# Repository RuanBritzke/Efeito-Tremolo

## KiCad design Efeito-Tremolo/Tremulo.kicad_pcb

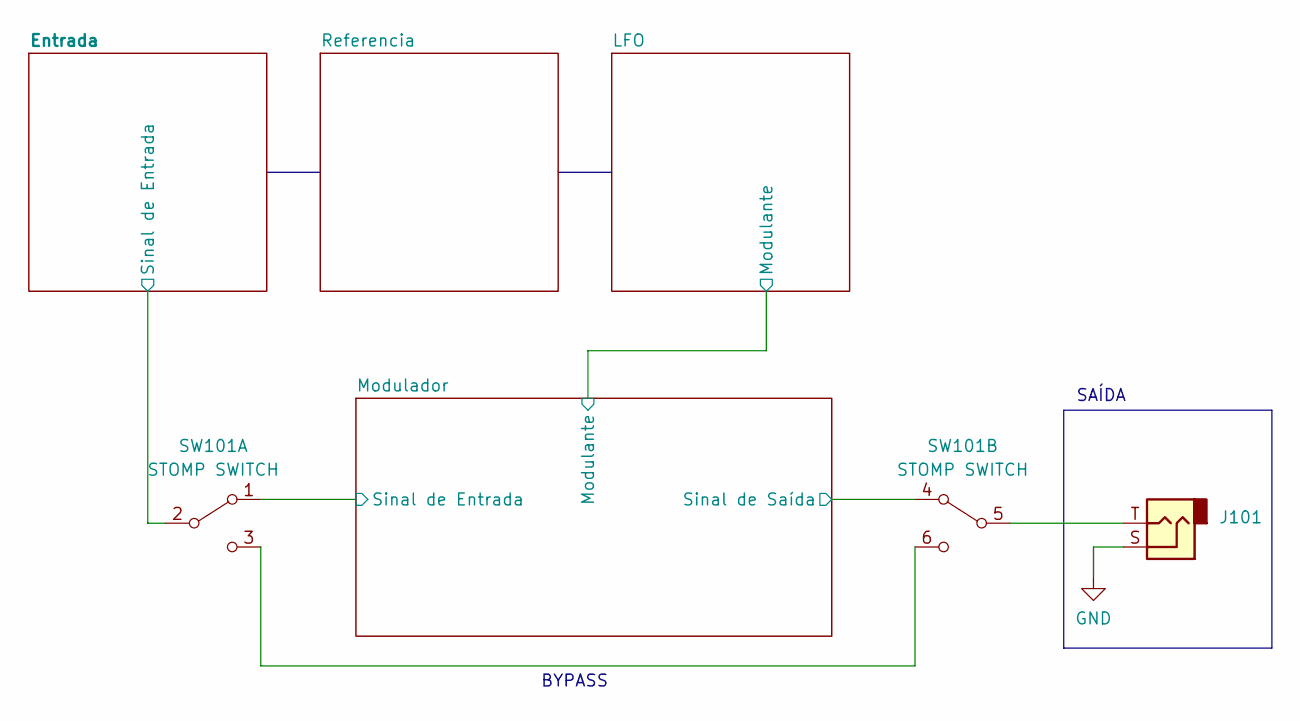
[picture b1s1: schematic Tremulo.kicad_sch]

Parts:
J101: AudioJack2; PinHeader_1x02_P2.54mm_Vertical
SW101: STOMP SWITCH; PinHeader_2x03_P2.54mm_Vertical

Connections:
/Entrada/Sinal de Entrada: SW101.2 (B); also elsewhere on the board
/Modulador/Sinal de Entrada: SW101.1 (A); also elsewhere on the board
/Modulador/Sinal de Saída: SW101.4 (A); also elsewhere on the board
GND: J101.S; also elsewhere on the board
unnamed: J101.T, SW101.5 (B)
unnamed: SW101.3 (C), SW101.6 (C)

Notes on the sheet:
BYPASS
SAÍDA

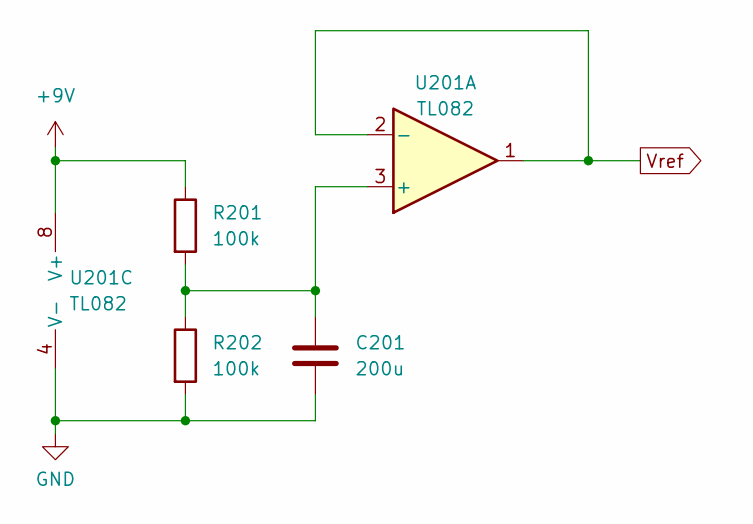
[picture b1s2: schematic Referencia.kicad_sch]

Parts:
C201: 200u; CP_Radial_D8.0mm_P5.00mm
R201, R202: 100k; R_Box_L8.4mm_W2.5mm_P5.08mm
U201: TL082; DIP-8_W7.62mm

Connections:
GND: C201.2, R202.2, U201.4 (V-); also elsewhere on the board
unnamed: C201.1, R201.2, R202.1, U201.3 (+)
Vref: U201.1, U201.2 (-); also elsewhere on the board

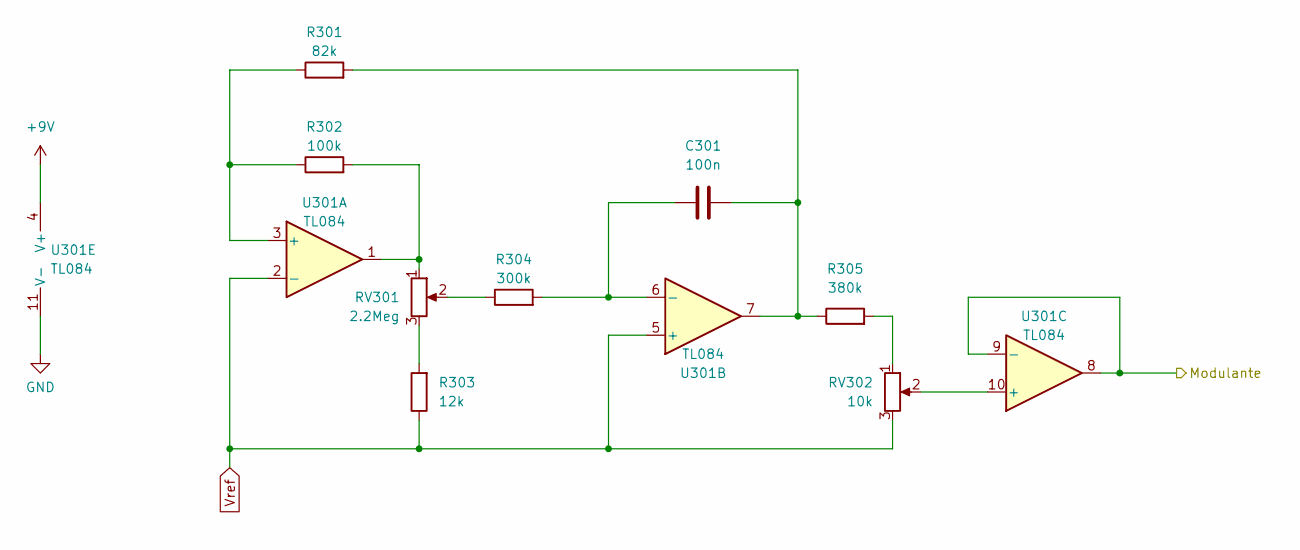
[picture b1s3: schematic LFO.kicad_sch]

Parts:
C301: 100n; CP_Radial_D8.0mm_P5.00mm
R301: 82k; R_Box_L8.4mm_W2.5mm_P5.08mm
R302: 100k; R_Box_L8.4mm_W2.5mm_P5.08mm
R303: 12k; R_Box_L8.4mm_W2.5mm_P5.08mm
R304: 300k; R_Box_L8.4mm_W2.5mm_P5.08mm
R305: 380k; R_Box_L8.4mm_W2.5mm_P5.08mm
RV301: 2.2Meg; PinHeader_1x03_P2.54mm_Vertical
RV302: 10k; PinHeader_1x03_P2.54mm_Vertical
U301: TL084; DIP-14_W7.62mm

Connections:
/LFO/Modulante: U301.8, U301.9 (-); also elsewhere on the board
GND: U301.11 (V-); also elsewhere on the board
unnamed: C301.1, R301.2, R305.1, U301.7
unnamed: C301.2, R304.2, U301.6 (-)
unnamed: R301.1, R302.1, U301.3 (+)
unnamed: R302.2, RV301.1, U301.1
unnamed: R303.2, RV301.3
unnamed: R304.1, RV301.2
unnamed: R305.2, RV302.1
unnamed: RV302.2, U301.10 (+)
Vref: R303.1, RV302.3, U301.2 (-), U301.5 (+); also elsewhere on the board

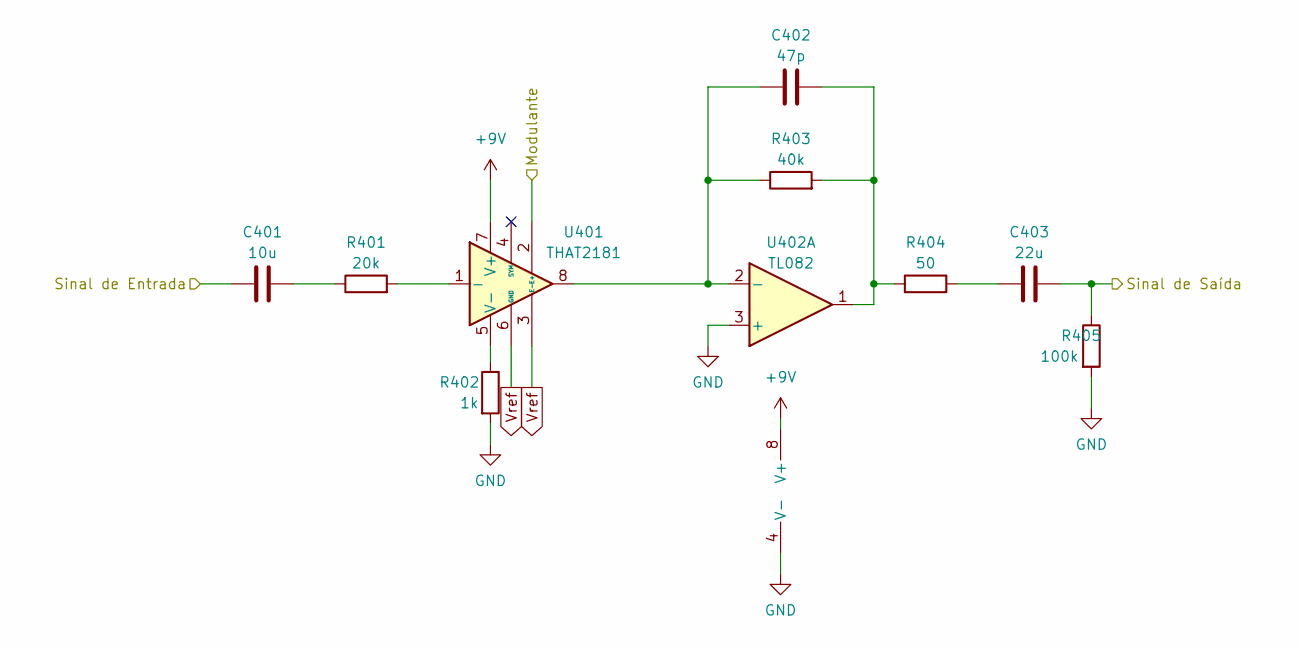
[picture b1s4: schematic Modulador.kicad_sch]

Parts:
C401: 10u; CP_Radial_D8.0mm_P5.00mm
C402: 47p; CP_Radial_D8.0mm_P5.00mm
C403: 22u; CP_Radial_D8.0mm_P5.00mm
R401: 20k; R_Box_L8.4mm_W2.5mm_P5.08mm
R402: 1k; R_Box_L8.4mm_W2.5mm_P5.08mm
R403: 40k; R_Box_L8.4mm_W2.5mm_P5.08mm
R404: 50; R_Box_L8.4mm_W2.5mm_P5.08mm
R405: 100k; R_Box_L8.4mm_W2.5mm_P5.08mm
U401: THAT2181; SIP-8_19x3mm_P2.54mm
U402: TL082; DIP-8_W7.62mm

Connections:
/LFO/Modulante: U401.2 (E+); also elsewhere on the board
/Modulador/Sinal de Entrada: C401.1; also elsewhere on the board
/Modulador/Sinal de Saída: C403.1, R405.1; also elsewhere on the board
GND: R402.2, R405.2, U402.3 (+), U402.4 (V-); also elsewhere on the board
unnamed: C401.2, R401.1
unnamed: C402.1, R403.1, U401.8, U402.2 (-)
unnamed: C402.2, R403.2, R404.2, U402.1
unnamed: C403.2, R404.1
unnamed: R401.2, U401.1 (-)
unnamed: R402.1, U401.5 (V-)
Vref: U401.3 (E-), U401.6 (GND); also elsewhere on the board

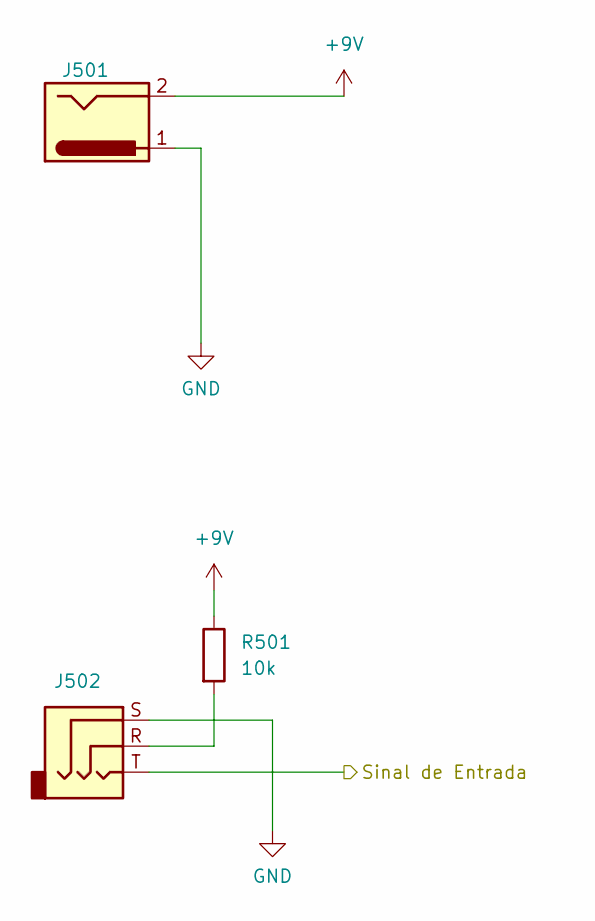
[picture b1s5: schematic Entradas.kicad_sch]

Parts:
J501: Barrel_Jack; PinHeader_1x02_P2.54mm_Vertical
J502: AudioJack3; PinHeader_1x03_P2.54mm_Vertical
R501: 10k; R_Box_L8.4mm_W2.5mm_P5.08mm

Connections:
/Entrada/Sinal de Entrada: J502.T; also elsewhere on the board
GND: J501.1, J502.S; also elsewhere on the board
unnamed: J502.R, R501.2

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
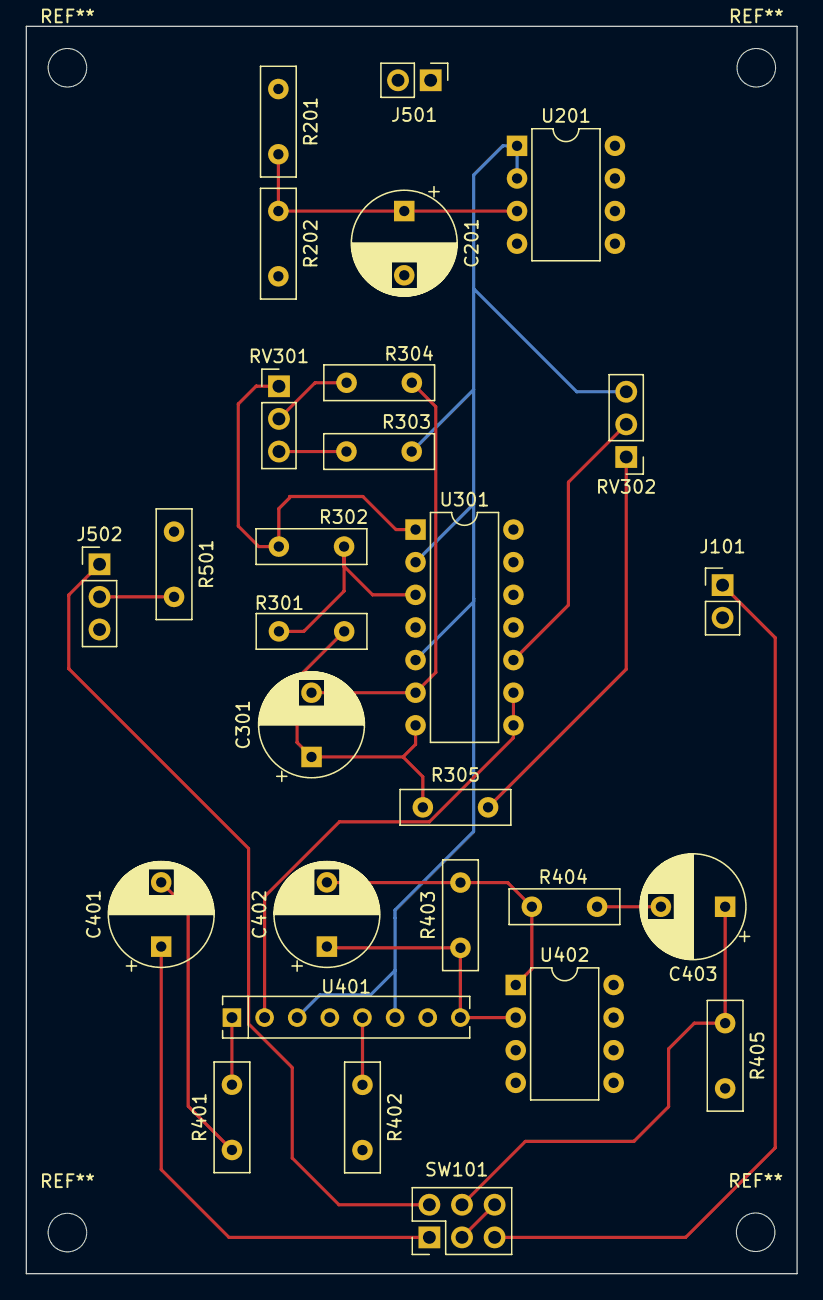
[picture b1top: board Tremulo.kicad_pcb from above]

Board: 4 copper layers, 60.0 x 97.1 mm, 28 parts (0 on the bottom side), 25 nets.

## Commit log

2022-07-08 Tremolo Effect
